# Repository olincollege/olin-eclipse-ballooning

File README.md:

# olin-eclipse-ballooning
Olin's National Eclipse Ballooning Project team repository

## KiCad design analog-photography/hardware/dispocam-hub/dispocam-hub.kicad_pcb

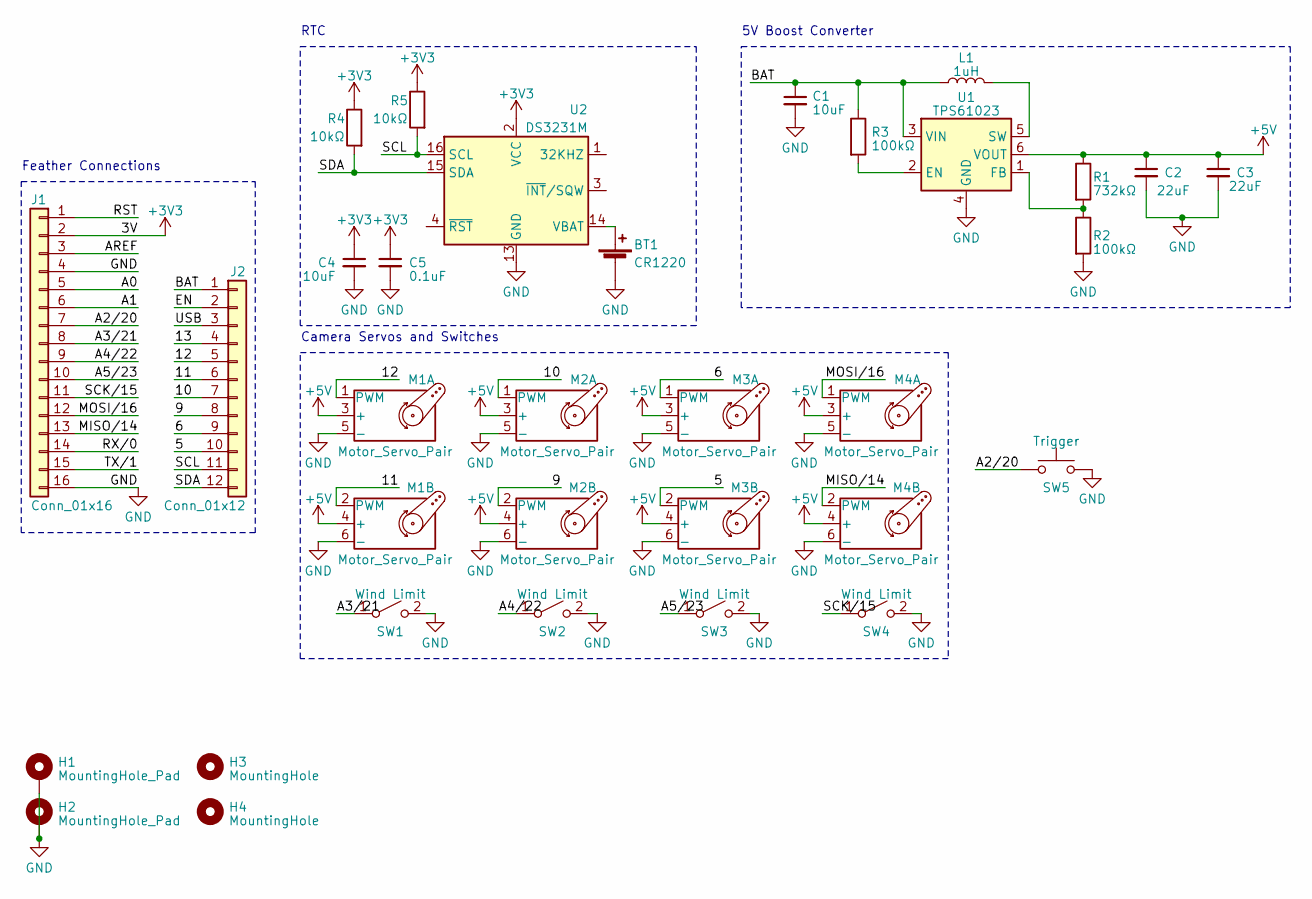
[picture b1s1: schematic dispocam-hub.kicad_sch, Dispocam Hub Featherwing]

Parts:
BT1: CR1220; BAT_BK-916-TR; Digikey Part # BK-916-CT-ND
C1, C4: 10uF; C_0603_1608Metric; Digikey Part # 1276-1871-1-ND
C2, C3: 22uF; C_0603_1608Metric; Digikey Part # 1276-1274-1-ND
C5: 0.1uF; C_0603_1608Metric; Digikey Part # 1276-CL10B104KB8NNNLCT-ND
H1, H2: MountingHole_Pad; MountingHole_0.1in_Pad
H3, H4: MountingHole; MountingHole_0.1in
J1: Conn_01x16; PinHeader_1x16_P2.54mm_Vertical
J2: Conn_01x12; PinHeader_1x12_P2.54mm_Vertical
L1: 1uH; L_Wuerth_MAPI-4030; Digikey Part # 732-11197-1-ND
M1, M2, M3, M4: Motor_Servo_Pair; PinHeader_2x03_P2.54mm_Vertical; Digikey Part # 609-3234-ND
R1: 732kΩ; R_0603_1608Metric; Digikey Part # 311-732KHRCT-ND
R2, R3: 100kΩ; R_0603_1608Metric; Digikey Part # 311-100KHRCT-ND
R4, R5: 10kΩ; R_0603_1608Metric; Digikey Part # RNCP0603FTD10K0CT-ND
SW1, SW2, SW3, SW4: Wind Limit; PinHeader_1x02_P2.54mm_Vertical
SW5: Trigger; SW_SPST_PTS810; Digikey Part # CKN10503CT-ND
U1: TPS61023; SOT-563; Digikey Part # 296-TPS61023DRLTCT-ND
U2: DS3231M; SOIC-16W_7.5x10.3mm_P1.27mm; Digikey Part # DS3231SN#-ND

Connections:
+3V3: C4.1, C5.1, J1.2, R4.1, R5.1, U2.2 (VCC)
+5V: C2.1, C3.1, M1.3 (+), M1.4 (+), M2.3 (+), M2.4 (+), M3.3 (+), M3.4 (+), M4.3 (+), M4.4 (+), R1.1, U1.6 (VOUT)
/5: J2.10, M3.2 (PWM)
/6: J2.9, M3.1 (PWM)
/9: J2.8, M2.2 (PWM)
/10: J2.7, M2.1 (PWM)
/11: J2.6, M1.2 (PWM)
/12: J2.5, M1.1 (PWM)
/13: J2.4
/A0: J1.5
/A1: J1.6
/A2/20: J1.7, SW5.1
/A3/21: J1.8, SW1.1 (A)
/A4/22: J1.9, SW2.1 (A)
/A5/23: J1.10, SW3.1 (A)
/AREF: J1.3
/BAT: C1.1, J2.1, L1.1, R3.1, U1.3 (VIN)
/EN: J2.2
/MISO/14: J1.13, M4.2 (PWM)
/MOSI/16: J1.12, M4.1 (PWM)
/RST: J1.1
/RX/0: J1.14
/SCK/15: J1.11, SW4.1 (A)
/SCL: J2.11, R5.2, U2.16 (SCL)
/SDA: J2.12, R4.2, U2.15 (SDA)
/TX/1: J1.15
/USB: J2.3
GND: BT1.2 (-), C1.2, C2.2, C3.2, C4.2, C5.2, H1.1, H2.1, J1.4, J1.16, M1.5 (-), M1.6 (-), M2.5 (-), M2.6 (-), M3.5 (-), M3.6 (-), M4.5 (-), M4.6 (-), R2.2, SW1.2 (B), SW2.2 (B), SW3.2 (B), SW4.2 (B), SW5.2, U1.4 (GND), U2.5 (GND), U2.6 (GND), U2.7 (GND), U2.8 (GND), U2.9 (GND), U2.10 (GND), U2.11 (GND), U2.12 (GND), U2.13 (GND)
unnamed: BT1.1 (+), U2.14 (VBAT)
unnamed: R3.2, U1.2 (EN)
unnamed: R1.2, R2.1, U1.1 (FB)
unnamed: L1.2, U1.5 (SW)

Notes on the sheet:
5V Boost Converter
RTC
Camera Servos and Switches
Feather Connections

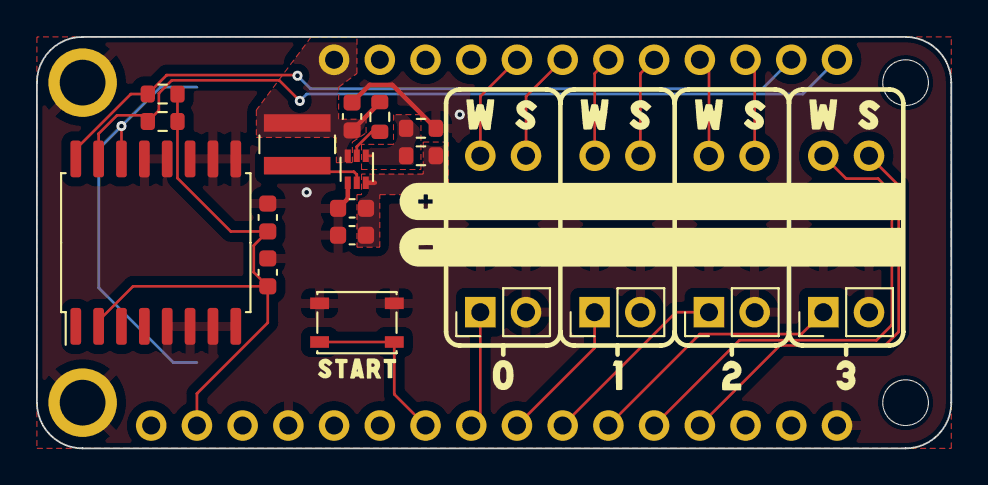
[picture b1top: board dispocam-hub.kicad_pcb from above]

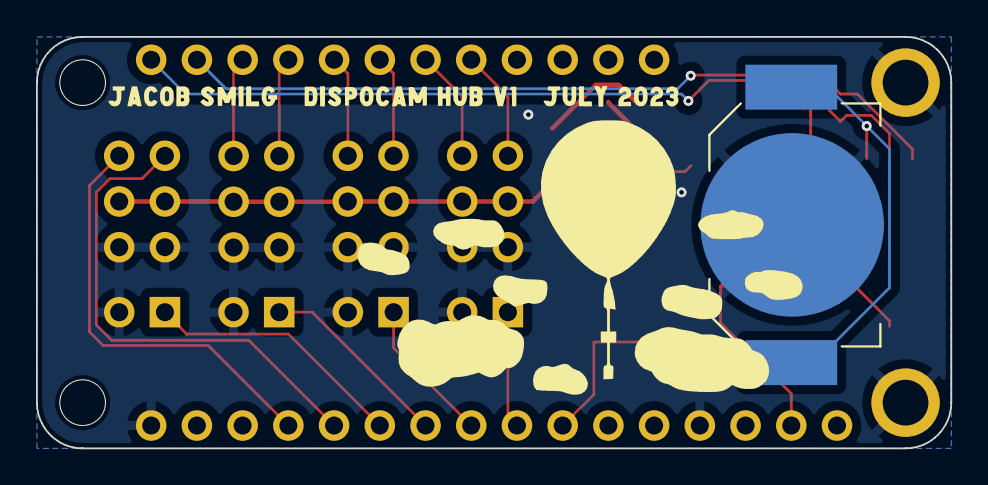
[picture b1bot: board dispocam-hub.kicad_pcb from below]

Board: 2 copper layers, 50.8 x 22.9 mm, 45 parts (4 on the bottom side), 23 nets.

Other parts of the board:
kibuzzard-64C40EF2: G***; kibuzzard-64C40EF2
kibuzzard-64C413B2, kibuzzard-64C413B2#2, kibuzzard-64C413B2#3, kibuzzard-64C413B2#4: G***; kibuzzard-64C413B2
kibuzzard-64C413C5, kibuzzard-64C413C5#2, kibuzzard-64C413C5#3, kibuzzard-64C413C5#4: G***; kibuzzard-64C413C5
kibuzzard-64C413FA: G***; kibuzzard-64C413FA
kibuzzard-64C418B2: G***; kibuzzard-64C418B2
kibuzzard-64C4164E: G***; kibuzzard-64C4164E
kibuzzard-64C4169B: G***; kibuzzard-64C4169B
kibuzzard-64C41670: G***; kibuzzard-64C41670
kibuzzard-64C41694: G***; kibuzzard-64C41694
kibuzzard-64C41698: G***; kibuzzard-64C41698

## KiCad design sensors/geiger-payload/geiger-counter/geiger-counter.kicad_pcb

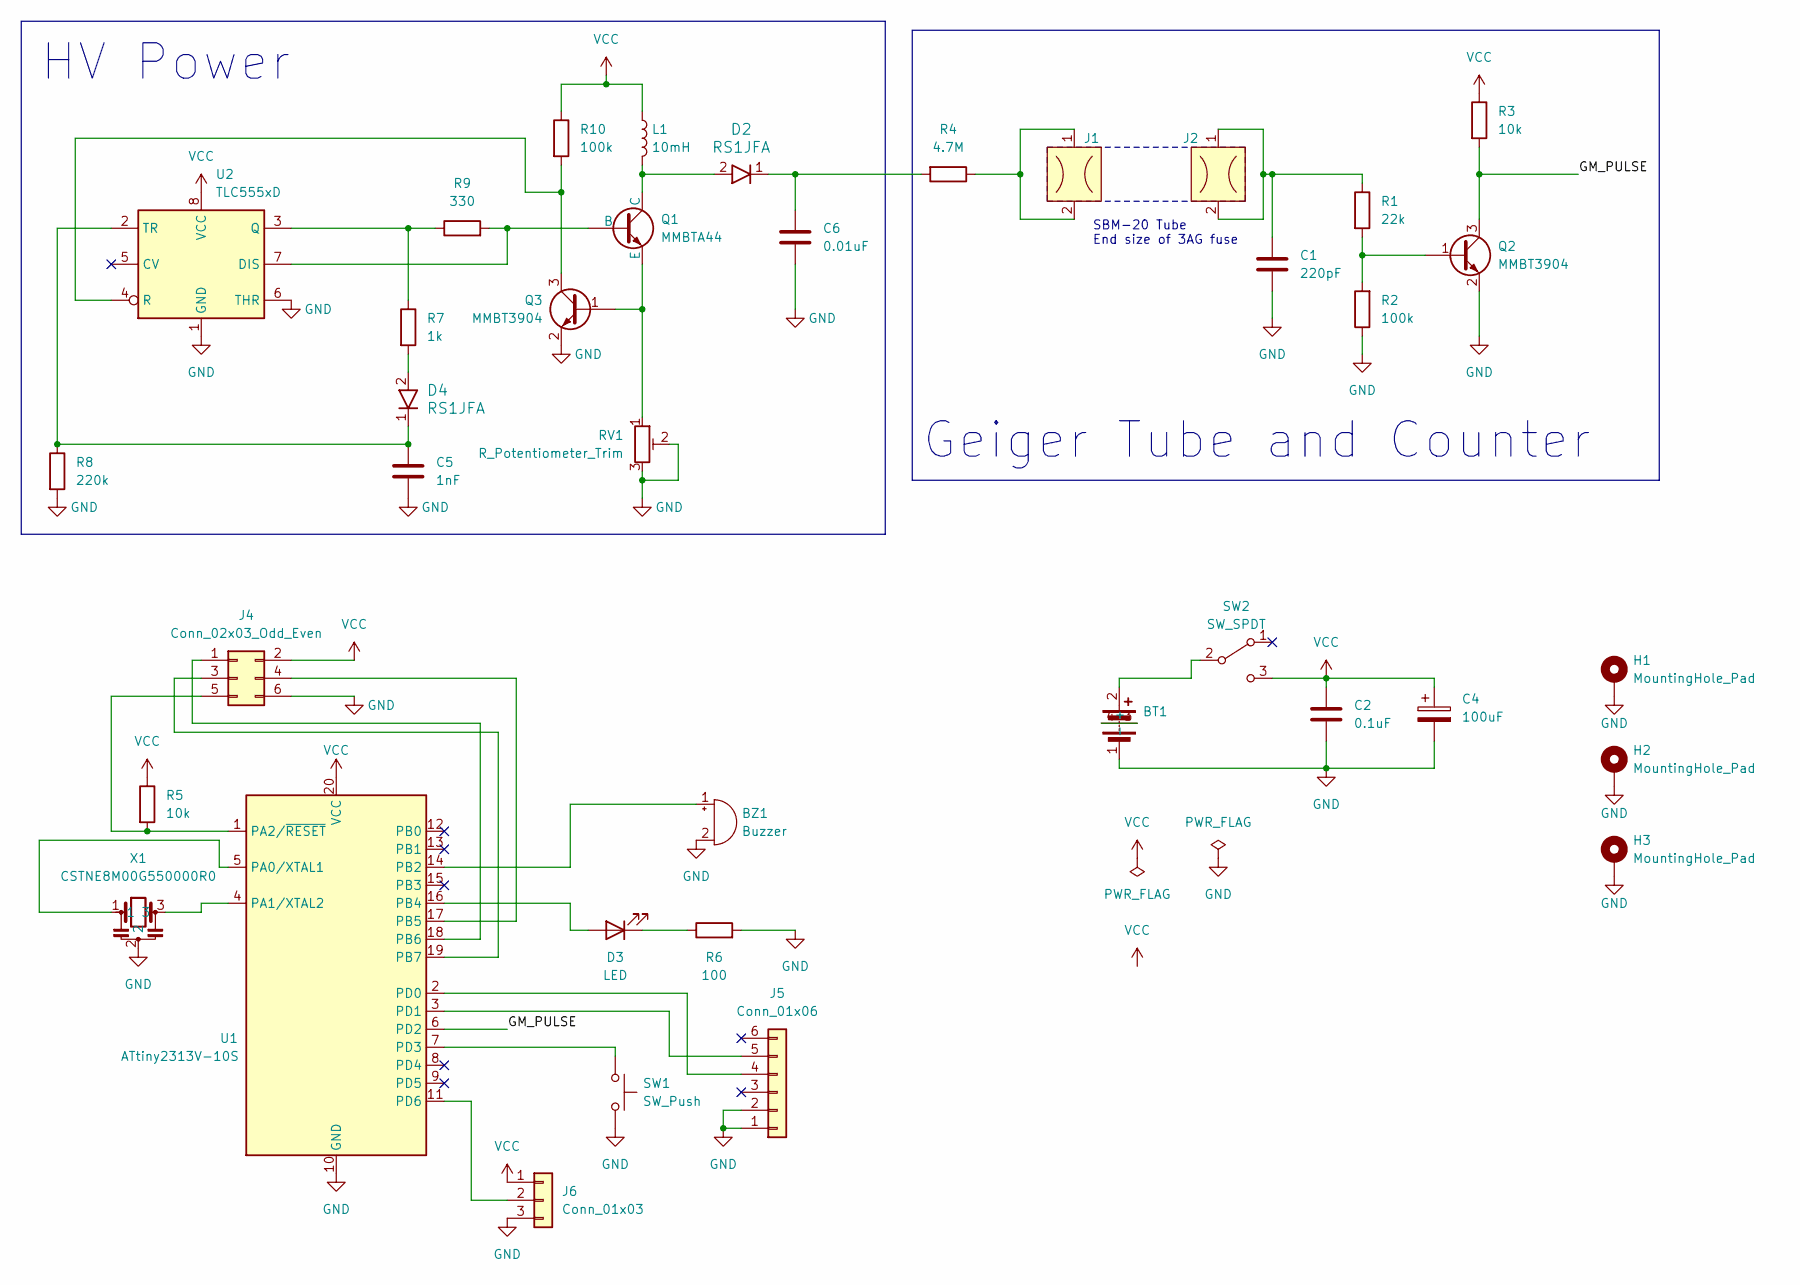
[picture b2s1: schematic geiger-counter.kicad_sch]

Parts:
BT1: 1022
BZ1: Buzzer; Buzzer_Mallory_AST1109MLTRQ
C1: 220pF; C_0805_2012Metric
C2: 0.1uF; C_0805_2012Metric
C4: 100uF; CP_Radial_D5.0mm_P2.00mm
C5: 1nF; C_0805_2012Metric
C6: 0.01uF; C_1206_3216Metric
D2, D4: RS1JFA; SOD-123FA_ONS
D3: LED; LED_0805_2012Metric
H1, H2, H3: MountingHole_Pad; MountingHole_2.2mm_M2_Pad
J1, J2: FUSE_3514
J4: Conn_02x03_Odd_Even; PinHeader_2x03_P2.54mm_Vertical
J5: Conn_01x06; PinHeader_1x06_P2.54mm_Vertical
J6: Conn_01x03; PinHeader_1x03_P2.54mm_Vertical
L1: 10mH; L_Changjiang_FNR6045S
Q1: MMBTA44; SOT-23
Q2, Q3: MMBT3904; SOT-23
R1: 22k; R_0805_2012Metric
R2, R10: 100k; R_0805_2012Metric
R3, R5: 10k; R_0805_2012Metric
R4: 4.7M; R_1206_3216Metric
R6: 100; R_0805_2012Metric
R7: 1k; R_0805_2012Metric
R8: 220k; R_0805_2012Metric
R9: 330; R_0805_2012Metric
RV1: R_Potentiometer_Trim; G43A
SW1: SW_Push; SW_Push_1P1T_XKB_TS-1187A
SW2: SW_SPDT; TP-33103
U1: ATtiny2313V-10S; SOIC-20W_7.5x12.8mm_P1.27mm
U2: TLC555xD; SOIC-8_3.9x4.9mm_P1.27mm
X1: CSTNE8M00G550000R0; CSTNE16M0V530000R0; Manufacturer_Part_Number CSTNE8M00G550000R0; Mouser Part Number 81-CSTNE8M00G550000R

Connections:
/GM_PULSE: Q2.3 (C), R3.2, U1.6 (PD2)
GND: BT1.1 (-), BZ1.2 (+), C1.2, C2.2, C4.2, C5.2, C6.2, H1.1, H2.1, H3.1, J4.6, J5.1, J5.2, J6.3, Q2.2 (E), Q3.2 (E), R2.1, R6.2, R8.2, RV1.2, RV1.3, SW1.2, U1.10 (GND), U2.1 (GND), U2.6 (THR), X1.2
unnamed: BT1.2 (+), SW2.2 (B)
unnamed: BT1.3, BT1.4
unnamed: BZ1.1 (-), U1.14 (PB2)
unnamed: C1.1, J2.1, J2.2, R1.1
unnamed: C6.1, D2.1, R4.2
unnamed: D3.2 (A), U1.16 (PB4)
unnamed: D3.1 (K), R6.1
unnamed: D4.2, R7.2
unnamed: J1.1, J1.2, R4.1
unnamed: J4.1, U1.18 (PB6)
unnamed: J4.3, U1.19 (PB7)
unnamed: J4.4, U1.17 (PB5)
unnamed: J4.5, R5.2, U1.1 (PA2/~RESET)
unnamed: J5.4, U1.2 (PD0)
unnamed: J5.5, U1.3 (PD1)
unnamed: J6.2, U1.11 (PD6)
unnamed: Q1.1 (B), R9.2, U2.7 (DIS)
unnamed: D2.2, L1.2, Q1.3 (C)
unnamed: Q1.2 (E), Q3.1 (B), RV1.1
unnamed: Q2.1 (B), R1.2, R2.2
unnamed: Q3.3 (C), R10.2, U2.4 (R)
unnamed: U1.5 (PA0/XTAL1), X1.1
unnamed: U1.4 (PA1/XTAL2), X1.3
unnamed: SW1.1, U1.7 (PD3)
unnamed: R7.1, R9.1, U2.3 (Q)
unnamed: C5.1, D4.1, R8.1, U2.2 (TR)
VCC: C2.1, C4.1, J4.2, J6.1, L1.1, R3.1, R5.1, R10.1, SW2.3 (C), U1.20 (VCC), U2.8 (VCC)

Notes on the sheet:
HV Power
Geiger Tube and Counter
SBM-20 Tube End size of 3AG fuse

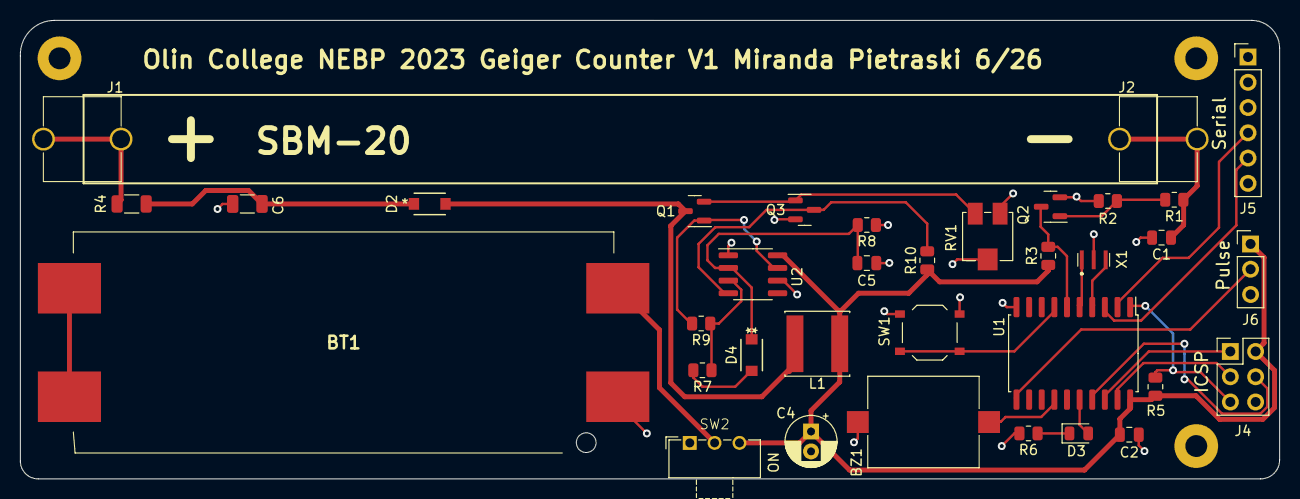
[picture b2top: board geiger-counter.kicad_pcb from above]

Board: 2 copper layers, 126.6 x 46.1 mm, 38 parts (0 on the bottom side), 29 nets.

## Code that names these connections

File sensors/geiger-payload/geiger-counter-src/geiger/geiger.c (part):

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	// send a pulse to the PULSE connector
	// a delay of 100us limits the max CPS to about 8000
	// you can comment out this code and increase the max CPS possible (up to 65535!)
	PORTD |= _BV(PD6);	// set PULSE output high
	_delay_us(PULSEWIDTH);
	PORTD &= ~(_BV(PD6));	// set pulse output low
		
	eventflag = 1;	// tell main program loop that a GM pulse has occurred
}
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{
	_delay_ms(25);					// slow down interrupt calls (crude debounce)
	
	if ((PIND & _BV(PD3)) == 0)		// is button still pressed?
		nobeep ^= 1;				// toggle mute mode
	
	EIFR |= _BV(INTF1);				// clear interrupt flag to avoid executing ISR again due to switch bounce
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	uint8_t i;	// index for fast mode
	tick = 1;	// update flag
	
	//PORTB ^= _BV(PB4);	// toggle the LED (for debugging purposes)
	cps = count;
	slowcpm -= buffer[idx];		// subtract oldest sample in sample buffer
	
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	if (eventflag) {		// a GM event has occurred, do something about it!
		eventflag = 0;		// reset flag as soon as possible, in case another ISR is called while we're busy

		PORTB |= _BV(PB4);	// turn on the LED
		
		if(!nobeep) {		// check if we're in mute mode
			TCCR0A |= _BV(COM0A0);	// enable OCR0A output on pin PB2
			TCCR0B |= _BV(CS01);	// set prescaler to clk/8 (1Mhz) or 1us/count
			OCR0A = 160;	// 160 = toggle OCR0A every 160ms, period = 320us, freq= 3.125kHz
		}
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		// 10ms delay gives a nice short flash and 'click' on the piezo
		_delay_ms(10);	
			
		PORTB &= ~(_BV(PB4));	// turn off the LED
		
		TCCR0B = 0;				// disable Timer0 since we're no longer using it
		TCCR0A &= ~(_BV(COM0A0));	// disconnect OCR0A from Timer0, this avoids occasional HVPS whine after beep
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	uart_putstring_P(PSTR(URL "\n"));

	// Set up AVR IO ports
	DDRB = _BV(PB4) | _BV(PB2);  // set pins connected to LED and piezo as outputs
	DDRD = _BV(PD6);	// configure PULSE output
	PORTD |= _BV(PD3);	// enable internal pull up resistor on pin connected to button
	
	// Set up external interrupts	
	// INT0 is triggered by a GM impulse
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	
	// Configure the Timers		
	// Set up Timer0 for tone generation
	// Toggle OC0A (pin PB2) on compare match and set timer to CTC mode
	TCCR0A = (0<<COM0A1) | (1<<COM0A0) | (0<<WGM02) |  (1<<WGM01) | (0<<WGM00);
	TCCR0B = 0;	// stop Timer0 (no sound)

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
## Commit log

2023-06-07 add payload dirs, analog photography pio project
2023-06-07 create main .gitignore and remove pio specific one
2023-06-08 change license to GNU GPLv3
2023-06-08 rename analog photography software folder
2023-06-08 create tracking cameras pio project
2023-06-08 start code for solar tracking with rtc
2023-06-08 remove .gitkeep
2023-06-08 calculate sun pos relative to Olin based on RTC
2023-06-12 write code for disposable camera control
2023-06-20 Add pcb design
2023-06-21 Add pcb corrections
2023-06-21 add shadow tracking files
2023-06-21 add board fixes
2023-06-21 silkscreen fix
2023-06-23 Update Sun Tracking - `main.cpp`
    Note: the current iteration of `main.cpp` is not yet operable. Allow update of the `SolTrack` library. Update functionality of the original `main.cpp` to include the stepper motors, IMU, and some log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
2023-06-23 pcb alterations due to part sourcing
2023-06-26 pcb design changes
2023-06-27 Refactor `main.cpp`
    Continue developing camera pan angle logic and fixing bugs.
2023-06-27 integrate GPS code
2023-06-27 add gps library
2023-06-28 remove reduntant absolute value function
2023-06-28 swap bno055 for bno08x
2023-06-28 add Adafruit_BNO08x library
2023-06-29 Update `main.cpp`
    Change pan and tilt pins due to changes in the electrical components. The configuration was moved from a breadboard to soldered connections.
2023-06-29 fix GPS float printouts
2023-06-30 update stepper motor test for two motors
2023-06-30 Update `main.cpp`
    Change the angles used in the `adjustCameraPanAngle` function from 0-360 degrees to -180-180 degrees allowing simpler calculation of forward/backward directional movement.
2023-06-30 add teensy env to platformio
2023-07-05 add iridium email sending program
2023-07-05 update pip instructions for windows
2023-07-05 improve wording
2023-07-06 Update microcontroller and stepper drivers
    Switch from Arduino Mega to the Teensy 4.1. Update stepper motor drivers to the A4988's.
2023-07-06 rewrite and simplify FSM code now only using one FSM to represent the camera, also moved debounce code to library for cleanliness
2023-07-07 Update Error Detection Logic
    Change error detection logic, improve code legibility, add additional print statements for debugging.
2023-07-07 remove unused functions, clean up constructor
2023-07-07 adjust shutter home position, simplify pressing state
2023-07-10 change servo min/max angle to 10-170 to avoid gear damage
2023-07-11 change pin and time threshold setting methods to allow for default constructor
2023-07-11 move camera code to library to simplify having multiple cameras
2023-07-11 rewrite for multiple cameras
2023-07-11 add default constructor and attach(), add missing getState()
2023-07-11 add camera attachment
2023-07-11 add camera index for debug purposes
2023-07-11 add debug messages, always set upper 4 bits of camsInTargetState to 1
2023-07-12 add kicad .gitignore to geiger counter
2023-07-12 create kicad project for analog photography payload
2023-07-13 Update stepper homing logic
    Update stepper homing logic and integrated the hall effect sensor into the stepper homing logic. Also refactor `platformio.ini`.
2023-07-21 add firmware and arduino code
2023-07-21 Update main.cpp
    Update the camera control logic.
2023-07-25 Update `main.cpp`
    Format code, correct stepper motor logic. Fix directional bug where stepper motors would travel in wrong direction.
2023-07-26 Update main.cpp
    debug tilt adjustment based on compass
2023-07-26 migrate to feather, add max pictures
2023-07-26 cleanup; remove unused functions and variables
2023-07-26 home both motors simultaneously
2023-07-26 move motors at the same time for smoother motion
2023-07-27 add file for inverted camera tracking
2023-07-28 add initial files for shadow tracking
2023-07-28 add disposable camera hub kicad project
2023-07-31 finalize PCB design, export gerbers, clean up schematic
2023-07-31 Incorporate shadow tracking code that reads from CSV on SD card
2023-09-30 wait for input if error
2023-10-02 redefine pins for PCB

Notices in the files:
sensors/geiger-payload/geiger-counter-src/geiger/geiger.c:
Copyright 2011 Jeff Keyzer, MightyOhm Engineering
This program is free software: you can redistribute it and/or modify
it under the terms of the GNU General Public License as published by
the Free Software Foundation, either version 3 of the License, or
(at your option) any later version.
